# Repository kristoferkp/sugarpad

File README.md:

# sugarpad

A versatile macropad powered by the RP2040 (Seeed Studio Xiao RP2040)

The sugarpad is powered by QMK (with VIA support).
sugarpad is a 11-key macropad with a rotary encoder (with built in switch) and an OLED screen.

The sugarpad is part of Hackclub's [Hackpad project](https://hackpad.hackclub.com/)!

## Firmware
With VIA, you can easily switch out the keymap of the macropad and record macros.

By default the 1st layer is a numpad, the rotary encoder play/pauses music and changes volume.
The keys under the encoder switch layers.

There are a total of 4 layers. 2nd and 3rd layers are F0-F21 and the final layer is unmapped.

By default the OLED screen shows the layer you are on.

## PCB
The PCB was built with KiCad.

## Case
The case can be printed in 3 parts - the bottom, the plate and the top. 
The case uses 4 M3x16 screws and 4 M3x5x4mm heatset inserts.

Small amount of supports are required (USB-C hole, heatset insert holes)

## BOM
- 1x Seeed Studio Xiao RP2040
- 1x EC11E Rotary Encoder (switch built in)
- 1x rotary Encoder Knob (can also be printed)
- 1x 0.91" SSD1306 OLED screen
- 11x Cherry MX style switches
- 11x Blank DSA keycaps
- 12x DO-35 diodes (THT)

## Case
- 4x M3x16mm socket head bolts
- 4x M3x5x4mm heatset inserts
- 1x top_case.step
- 1x plate.step
- 1x bottom_case.step

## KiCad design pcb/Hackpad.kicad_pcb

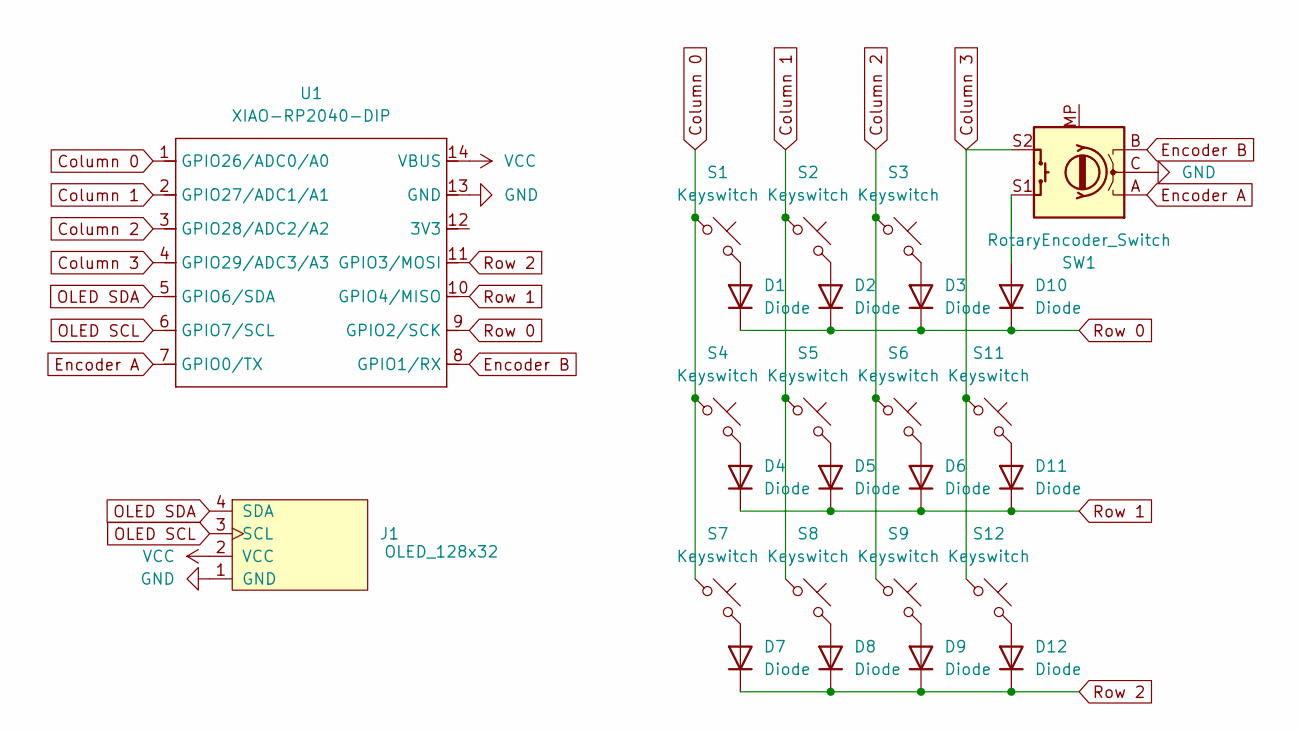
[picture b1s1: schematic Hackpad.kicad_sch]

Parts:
D1, D2, D3, D4, D5, D6, D7, D8, D9, D10, D11, D12: Diode; Diode_DO-35
J1: OLED_128x32
S1, S2, S3, S4, S5, S6, S7, S8, S9, S11, S12: Keyswitch; MX_PCB_1.00u
SW1: RotaryEncoder_Switch; RotaryEncoder_Alps_EC11E-Switch_Vertical_H20mm_MountingHoles
U1: XIAO-RP2040-DIP; Seeed_XIAO_RP2040

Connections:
Column 0: S1.1, S4.1, S7.1, U1.1 (GPIO26/ADC0/A0)
Column 1: S2.1, S5.1, S8.1, U1.2 (GPIO27/ADC1/A1)
Column 2: S3.1, S6.1, S9.1, U1.3 (GPIO28/ADC2/A2)
Column 3: S11.1, S12.1, SW1.S2, U1.4 (GPIO29/ADC3/A3)
Encoder A: SW1.A, U1.7 (GPIO0/TX)
Encoder B: SW1.B, U1.8 (GPIO1/RX)
GND: J1.1 (GND), SW1.C, U1.13 (GND)
unnamed: D1.2 (A), S1.2
unnamed: D2.2 (A), S2.2
unnamed: D3.2 (A), S3.2
unnamed: D4.2 (A), S4.2
unnamed: D5.2 (A), S5.2
unnamed: D6.2 (A), S6.2
unnamed: D7.2 (A), S7.2
unnamed: D8.2 (A), S8.2
unnamed: D9.2 (A), S9.2
unnamed: D10.2 (A), SW1.S1
unnamed: D11.2 (A), S11.2
unnamed: D12.2 (A), S12.2
OLED SCL: J1.3 (SCL), U1.6 (GPIO7/SCL)
OLED SDA: J1.4 (SDA), U1.5 (GPIO6/SDA)
Row 0: D1.1 (K), D2.1 (K), D3.1 (K), D10.1 (K), U1.9 (GPIO2/SCK)
Row 1: D4.1 (K), D5.1 (K), D6.1 (K), D11.1 (K), U1.10 (GPIO4/MISO)
Row 2: D7.1 (K), D8.1 (K), D9.1 (K), D12.1 (K), U1.11 (GPIO3/MOSI)
VCC: J1.2 (VCC), U1.14 (VBUS)

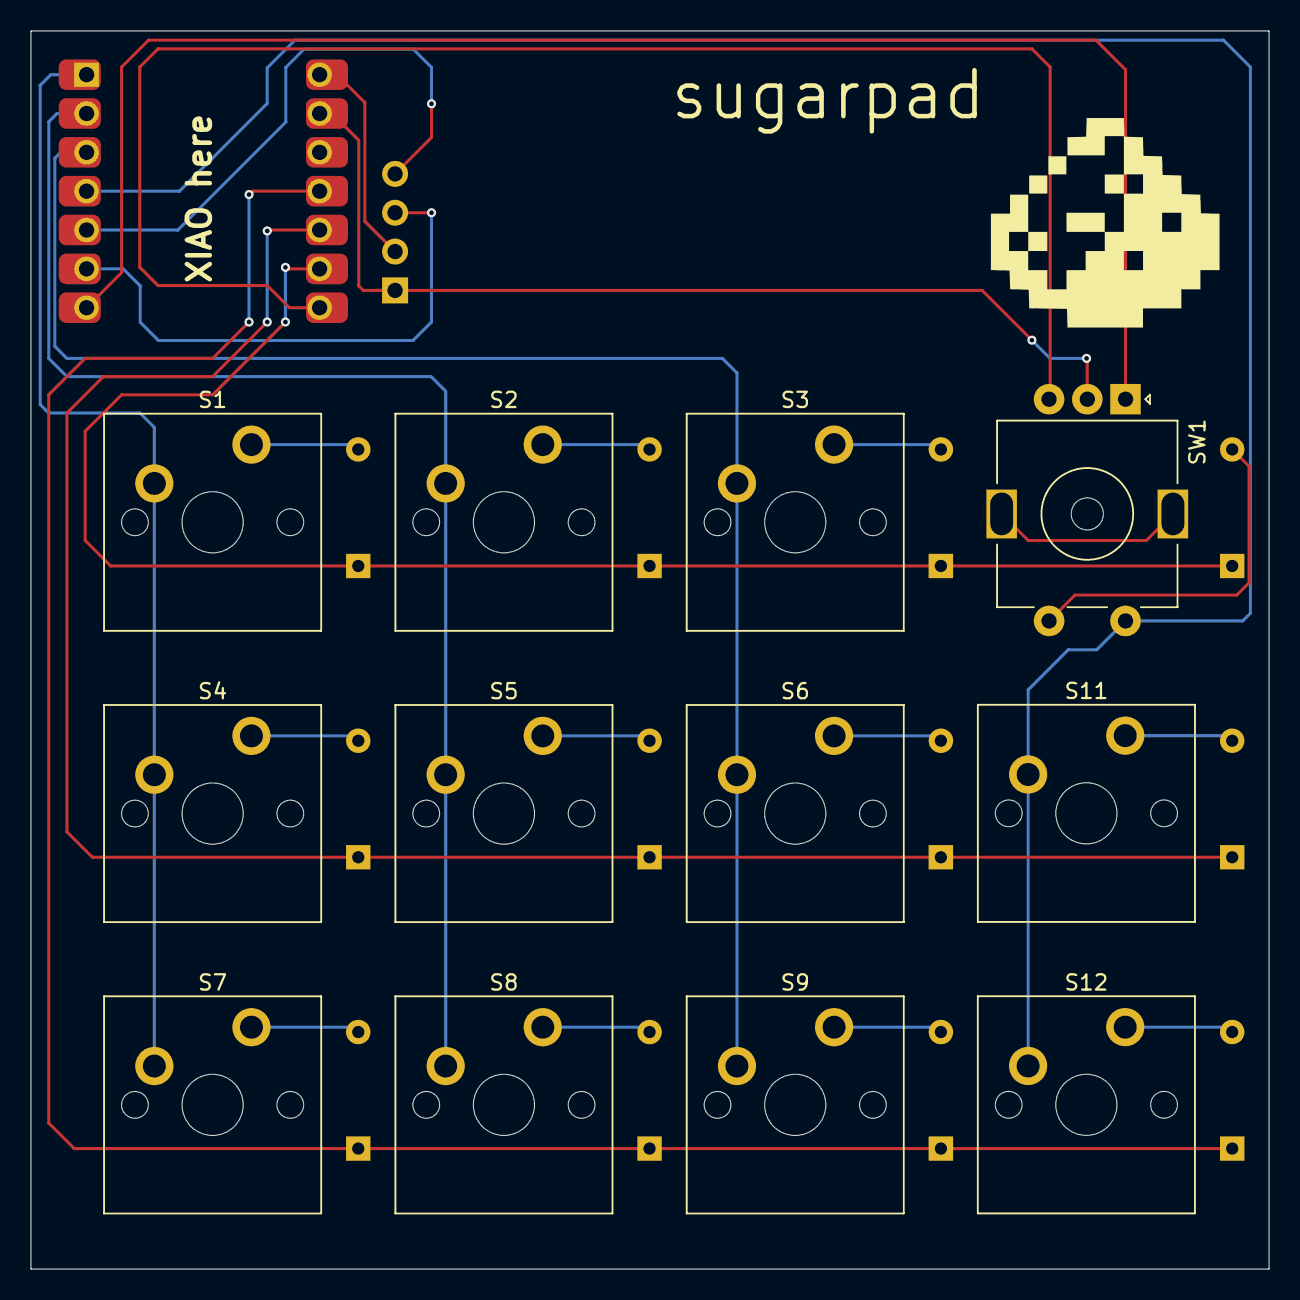
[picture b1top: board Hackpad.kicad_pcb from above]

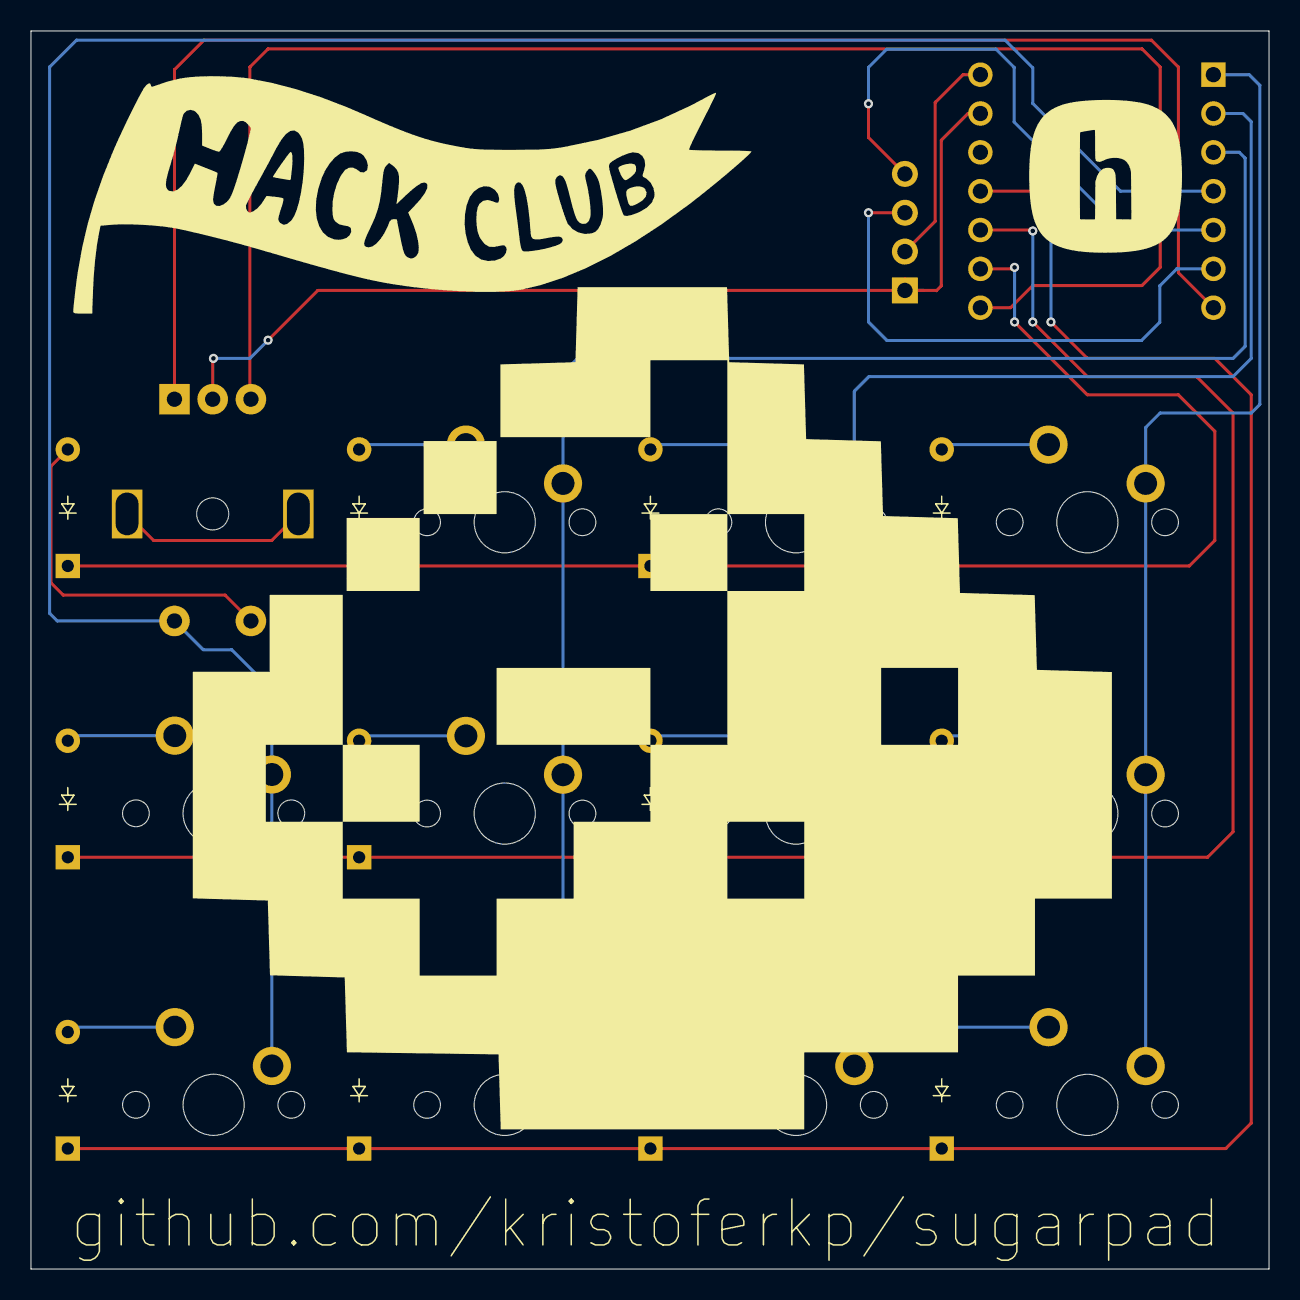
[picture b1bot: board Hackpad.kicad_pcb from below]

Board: 2 copper layers, 81.0 x 81.0 mm, 26 parts (12 on the bottom side), 25 nets.

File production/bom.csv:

Designator,Footprint,Quantity,Value,LCSC Part #
"D1, D10, D11, D12, D2, D3, D4, D5, D6, D7, D8, D9",Diode_DO-35,12,Diode,
J1,OLED_128x32,1,OLED_128x32,
"S1, S11, S12, S2, S3, S4, S5, S6, S7, S8, S9",MX_PCB_1.00u,11,Keyswitch,
SW1,RotaryEncoder_Alps_EC11E-Switch_Vertical_H20mm_MountingHoles,1,RotaryEncoder_Switch,
U1,Seeed_XIAO_RP2040,1,XIAO-RP2040-DIP,

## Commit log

2025-06-28 added firmware - qmk (via compatible)
2025-06-28 added needed files maybe
2025-06-28 added gif of exploded view
2025-06-28 readme updated
2025-06-28 added step files
2025-06-28 accidentally exported knob as f3d
2025-06-28 added firmware to production
2025-06-28 added gitignore and final image
2025-07-13 fixed plate
2025-07-13 actually fixed the file
